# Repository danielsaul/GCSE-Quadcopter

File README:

#Quadcopter
##© Copyright Daniel Saul

My GCSE Quadcopter project: the aim of which is to create a fully-functional, four rotored, remote control helicopter from scratch. 
Uses a custom designed PCB with an atmega3280 as the core microcontroller, usign the arduino bootloader.

The IMU is made up of a 3-axis accelerometer, a 2-axis gyro and a 1-axis gyro to get 6 degrees of freedom. There is the possibility of extending this to include a magnetometer and GPS in the future.

There will also be an ultrasonic rangefinder on board for low-level altitude control.

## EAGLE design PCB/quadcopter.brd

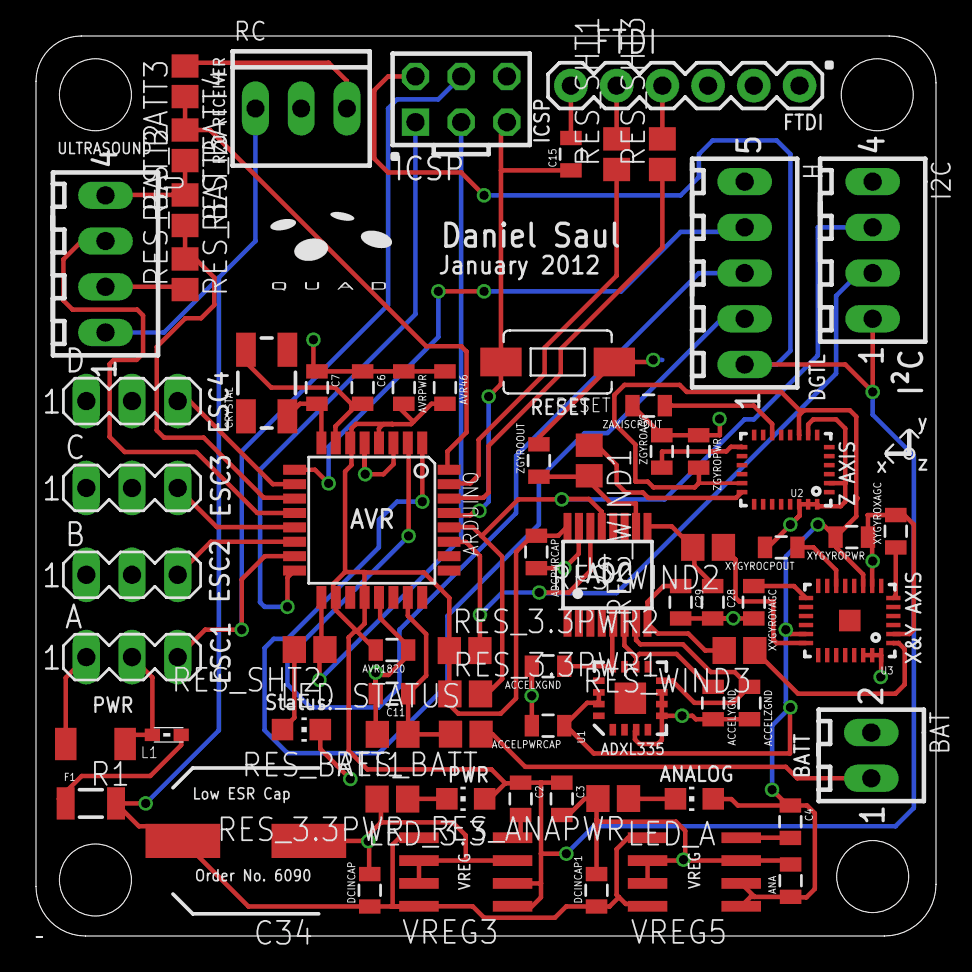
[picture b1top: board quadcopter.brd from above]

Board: 2 copper layers, 50.0 x 50.0 mm, 72 parts (1 on the bottom side), 51 nets.

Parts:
A: Motor A; MA03-1
ACCELPWRCAP: 100nF; 0805
ACCELXGND: 100nF; 0805
ACCELYGND: 100nF; 0805
ACCELZGND: 100nF; 0805
ADCPWRCAP: 100nF; 0805
ANA: 10uF; 0805
ARDUINO: ATMEGA328; TQFP32-08
AVR46, AVR1820: 100nF; 0805
AVRPWR: 100nF; 0805
B: MA03-1
BAT: Unreg Battery; 6410-02
C: MA03-1
C2, C4: 0.01uF; 0805
C3: 10uF; 0805
C6, C7: 18pF; 0805
C11, C15, C28, C29: 100nF; 0805
C34: 150uF; SANYO-OSCON_SMD_E7
CRYSTAL: 16MHz; CRYSTAL-SMD-5X3
D: MA03-1
DCINCAP, DCINCAP1: 1uF; 0805
F1: PTC Fuse; PTC-1206
FTDI: FTDI_BASICPTH; FTDI_BASIC
H: 6410-05
I2C: 6410-04
ICSP: AVR-ISP-6
L1: Ferrite Bead; 0603
LED_3.3: red; CHIP-LED0805
LED_A: red; CHIP-LED0805
LED_STATUS: blue; CHIP-LED0805
R1: VARISTOR; CT/CN1206
RC: RC-IN; 22-23-2031
RESET: TACTILE-SWITCH-1101NE
RES_3.3PWR: 100R; R0805
RES_3.3PWR1, RES_3.3PWR2: 4K7; R0805
RES_ANAPWR: 100R; R0805
RES_BATT: 100K; R0805
RES_BATT1, RES_BATT2, RES_BATT4: 10K; R0805
RES_BATT3, RES_BATT5: 22k; R0805
RES_SHT1: 1K; R0805
RES_SHT2, RES_SHT3: 100R; R0805
RES_WIND1, RES_WIND2, RES_WIND3: 750R; R0805
U: SRF05; 6410-04
U1: ADXL335; LFCSP-16
U2: ISZ500SMD; QFN-28_6X8
U3: IDG500; SPARKFUN_IDG500
U$1: LOGO
U$2: MAX11615; QSOP16
VREG3, VREG5: LT1763CS8-3.3; SOIC8
XYGYROCPOUT: 100nF; 0805
XYGYROPWR: 100nF; 0805
XYGYROXAGC: .22uF; 0805
XYGYROYAGC: .22uF; 0805
ZAXISCPOUT: 100nF; 0805
ZGYROAGC: 0.22uF; 0805
ZGYROOUT: 100nF; 0805
ZGYROPWR: 100nF; 0805

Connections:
3.3V: ADCPWRCAP.1, ARDUINO.4, ARDUINO.6, ARDUINO.18, ARDUINO.20, AVR46.2, AVR1820.2, AVRPWR.2, C2.1, C3.1, H.1, I2C.1, ICSP.2, LED_3.3.A, RES_3.3PWR1.1, RES_3.3PWR2.1, U$2.16, VREG3.1, VREG3.2
3.3VANALOG: ACCELPWRCAP.1, ANA.1, C4.1, LED_A.A, U1.14, U1.15, U2.9, U2.19, U3.9, U3.19, VREG5.1, VREG5.2, XYGYROPWR.2, ZGYROPWR.2
16: ARDUINO.16, ICSP.1
ACCELX: ACCELXGND.1, U1.12, U$2.5
ACCELY: ACCELYGND.1, U1.10, U$2.6
ACCELZ: ACCELZGND.1, U1.8, U$2.7
ALT-IN: ARDUINO.11, RES_BATT2.2, RES_BATT3.1
ALT-OUT: ARDUINO.12, U.3
BATTREAD: ARDUINO.23, C11.1, RES_BATT.2, RES_BATT1.1
DCIN: C34.+, DCINCAP.1, DCINCAP1.1, F1.2, RC.1, U.1, VREG3.5, VREG3.8, VREG5.5, VREG5.8
DIGITAL3-PWM: ARDUINO.1, H.2
DIGITAL4: ARDUINO.2, H.3
DIGITAL5: ARDUINO.9, H.4
GND: A.1, ACCELPWRCAP.2, ACCELXGND.2, ACCELYGND.2, ACCELZGND.2, ADCPWRCAP.2, ANA.2, ARDUINO.3, ARDUINO.5, ARDUINO.21, AVR46.1, AVR1820.1, AVRPWR.1, BAT.2, C3.2, C6.1, C7.1, C11.2, C28.2, C29.2, C34.-, DCINCAP.2, DCINCAP1.2, FTDI.GND, H.5, I2C.4, ICSP.6, LED_STATUS.C, R1.2, RC.2, RESET.P$1, RES_3.3PWR.2, RES_ANAPWR.2, RES_BATT1.2, RES_BATT3.2, RES_BATT5.2, U.4, U1.3, U1.5, U1.6, U1.7, U2.2, U2.8, U2.26, U2.27, U2.28, U3.2, U3.8, U3.26, U3.27, U3.28, U$2.15, VREG3.3, VREG3.6, VREG3.7, VREG5.3, VREG5.6, VREG5.7, XYGYROCPOUT.2, XYGYROPWR.1, XYGYROXAGC.2, XYGYROYAGC.2, ZAXISCPOUT.2, ZGYROAGC.2, ZGYROOUT.2, ZGYROPWR.1
GYROX: C29.1, RES_WIND3.2, U$2.8
GYROY: C28.1, RES_WIND2.2, U$2.9
GYROZ: RES_WIND1.2, U$2.10, ZGYROOUT.1
unnamed: C4.2, VREG5.4
unnamed: BAT.1, RES_BATT.1
unnamed: LED_3.3.C, RES_3.3PWR.1
unnamed: C2.2, VREG3.4
unnamed: LED_A.C, RES_ANAPWR.1
unnamed: ARDUINO.7, C6.2, CRYSTAL.3
unnamed: ARDUINO.8, C7.2, CRYSTAL.1
unnamed: FTDI.RXI, RES_SHT1.2
unnamed: FTDI.TXO, RES_SHT3.2
unnamed: C15.2, FTDI.DTR
unnamed: F1.1, L1.2
unnamed: RES_BATT2.1, U.2
unnamed: ARDUINO.17, ICSP.3, RES_SHT2.1
unnamed: LED_STATUS.A, RES_SHT2.2
unnamed: RC.3, RES_BATT4.1
unnamed: U2.15, ZGYROAGC.1
unnamed: U2.12, ZAXISCPOUT.1
unnamed: RES_WIND1.1, U2.20
unnamed: U3.15, XYGYROYAGC.1
unnamed: U3.12, XYGYROCPOUT.1
unnamed: U3.6, XYGYROXAGC.1
unnamed: RES_WIND2.1, U3.20
unnamed: RES_WIND3.1, U3.1
PWMA: A.3, ARDUINO.15, ICSP.4
PWMB: ARDUINO.14, B.3
PWMC: ARDUINO.13, C.3
PWMD: ARDUINO.10, D.3
RC-IN1: ARDUINO.31, RES_SHT1.1
RC-IN2: ARDUINO.30, RES_SHT3.1
RESET_PIN: ARDUINO.29, C15.1, ICSP.5, RESET.P$2
RX-PPM: ARDUINO.32, RES_BATT4.2, RES_BATT5.1
S: A.2, L1.1, R1.1
SCL: ARDUINO.28, I2C.3, RES_3.3PWR1.2, U$2.13
SDA: ARDUINO.27, I2C.2, RES_3.3PWR2.2, U$2.14

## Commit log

2011-09-21 Finished schematic
2011-12-30 Updated Repo
2011-12-30 Reduced project folder size
2011-12-30 renamed readme
2011-12-30 Replaced projectfolder with latest one
2012-01-06 PCB development in project folder
2012-01-13 Started programming, updated folder
2012-01-23 Start receiver code
2012-01-25 Receiver interrupt code done
2012-02-17 Continued with receiver & fixed bits
2012-02-28 Folder work
2012-03-26 Frame Sketchup done. ADC firmware added.
2012-04-03 Loads of stuff
2012-04-03 Added starts of accel.h
2012-04-03 Accel Calibration and measurement routines written
2012-04-03 Corrected README
2012-04-03 Added necessary libraries. Fixed accel, changed variable types to float
2012-04-04 Gyro calibration routine written
2012-04-04 Measure gyro written - can now get radians/s for each axis
2012-04-08 Altered PID, gyroRate is ADC value temporarily & trying to get vaguely level hover
2012-04-13 Updated project folder. Gyro-only throttle up/down firmware done.
2012-04-13 Updated Project Folder
2012-04-13 Standardized Variable Names
2012-04-14 Storing calibrated sensor offsets in EEPROM.
2012-04-15 Added calibration command from tx & started sorting 100Hz loop
2012-04-15 Fourth Order Filter from AeroQuad implemented
2012-04-16 Folder work & pretty tx diagram
2012-04-16 Pretty Instruction Card Done.
2012-04-17 Started motor control bits in 100Hz loop
2012-04-18 PID, Main loop, project folder etc.
2012-04-19 Squashed some bugs
2012-04-19 Squashed another bug.. missing '&'s, grrr
2012-04-20 Fixed some type conversions on readadc, added yawhold.h
